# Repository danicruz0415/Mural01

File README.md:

# Mural01
Design files, 3D models, cuts and circuits used for my first mural

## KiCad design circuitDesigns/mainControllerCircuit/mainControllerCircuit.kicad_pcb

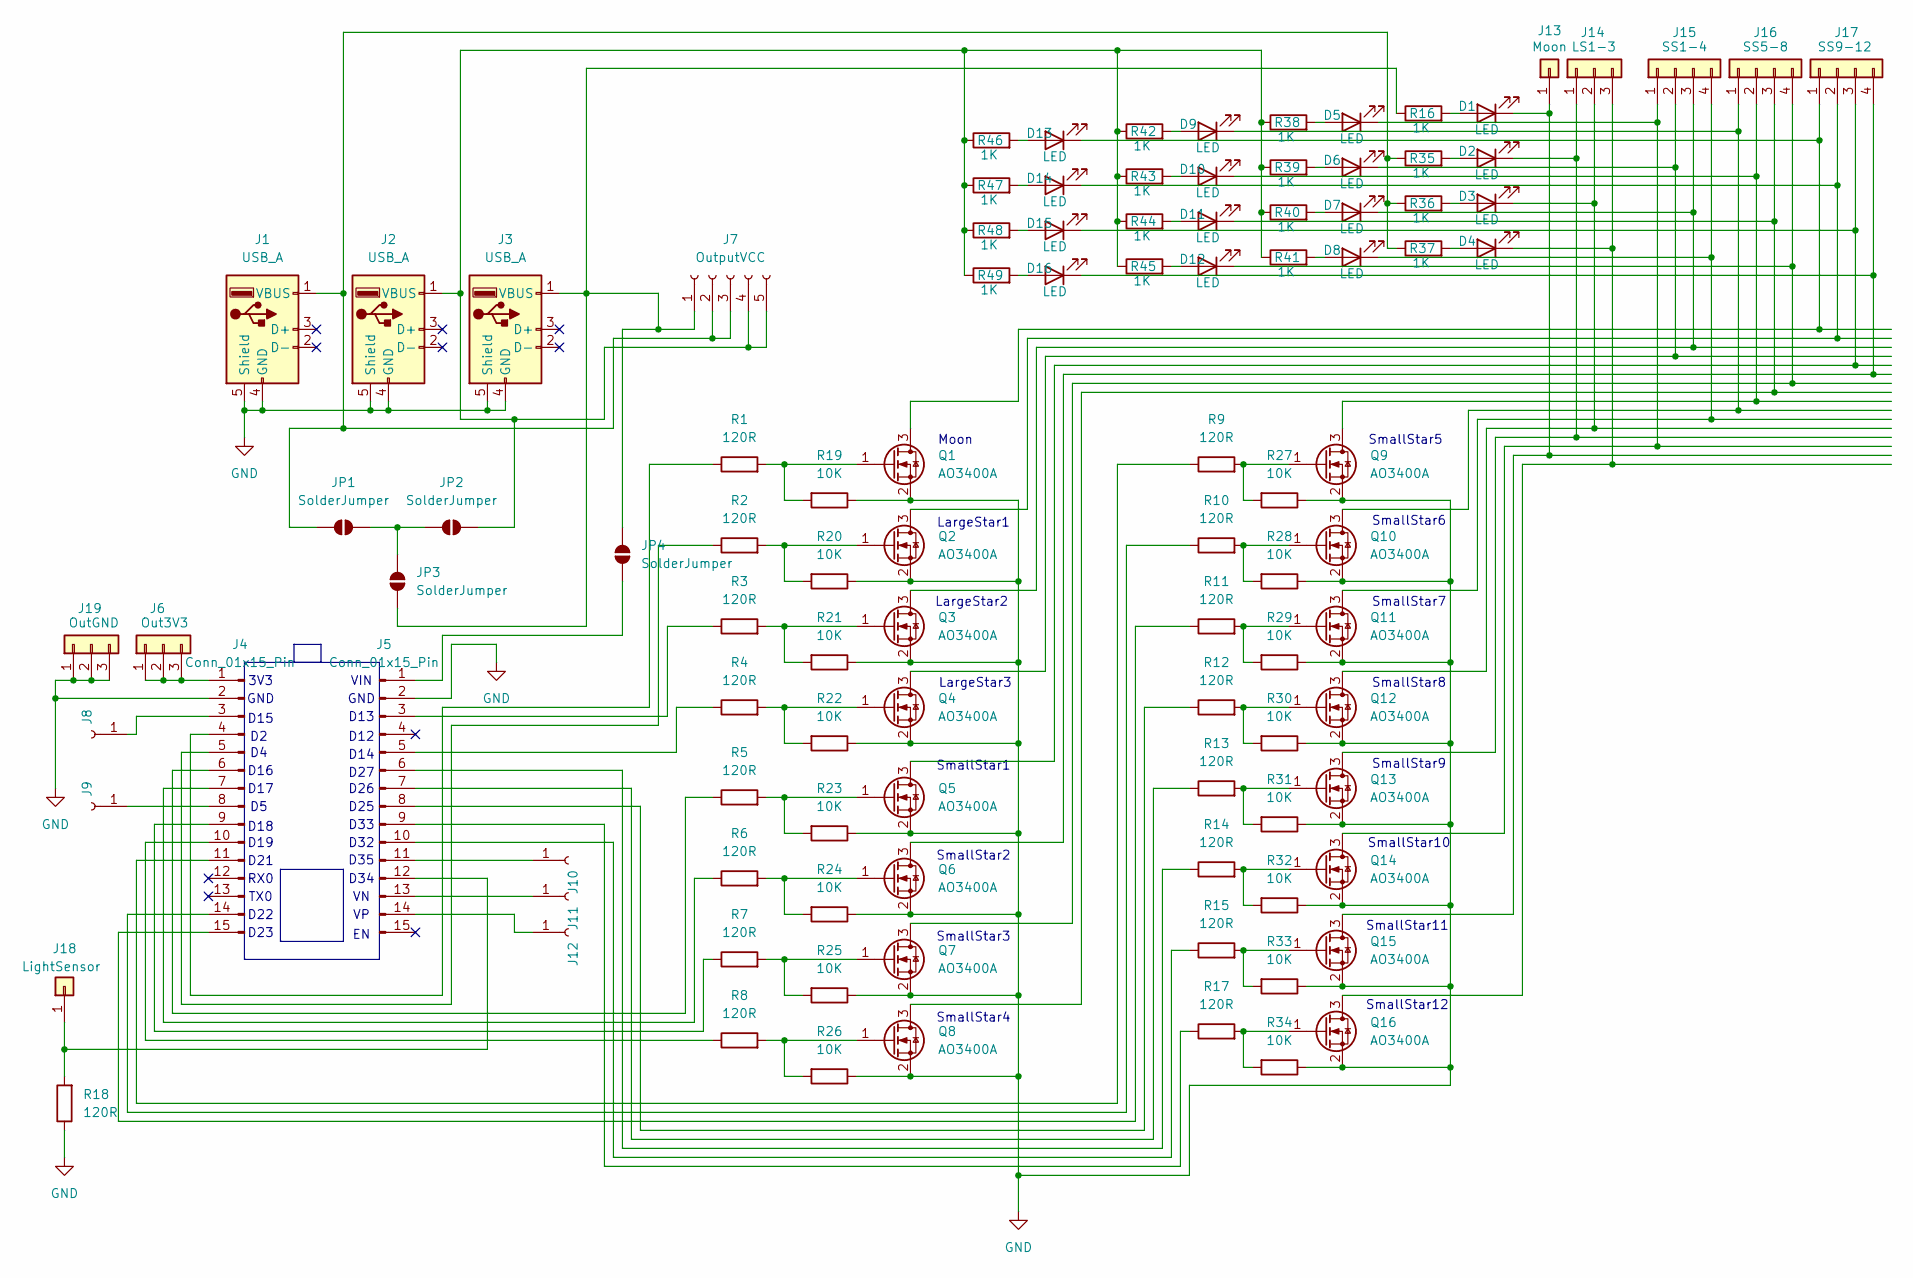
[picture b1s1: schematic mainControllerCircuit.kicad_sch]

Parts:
D1, D2, D3, D4, D5, D6, D7, D8, D9, D10, D11, D12, D13, D14, D15, D16: LED; LED_D3.0mm
J1, J2, J3: USB_A; USB_A_Molex_67643_Horizontal
J4, J5: Conn_01x15_Pin; PinSocket_1x15_P2.54mm_Vertical
J6: Out3V3; PinSocket_1x03_P2.54mm_Vertical
J7: OutputVCC; PinSocket_1x05_P2.54mm_Vertical
J8, J9, J10, J11, J12: PinSocket_1x01_P2.54mm_Vertical
J13: Moon; PinSocket_1x01_P2.54mm_Vertical
J14: LS1-3; PinSocket_1x03_P2.54mm_Vertical
J15: SS1-4; PinSocket_1x04_P2.54mm_Vertical
J16: SS5-8; PinSocket_1x04_P2.54mm_Vertical
J17: SS9-12; PinSocket_1x04_P2.54mm_Vertical
J18: LightSensor; PinSocket_1x01_P2.54mm_Vertical
J19: OutGND; PinSocket_1x03_P2.54mm_Vertical
JP1, JP2, JP3, JP4: SolderJumper; PinSocket_1x02_P2.54mm_Vertical
Q1, Q2, Q3, Q4, Q5, Q6, Q7, Q8, Q9, Q10, Q11, Q12, Q13, Q14, Q15, Q16: AO3400A; SOT-23
R1, R2, R3, R4, R5, R6, R7, R8, R9, R10, R11, R12, R13, R14, R15, R17, R18: 120R; R_Axial_DIN0207_L6.3mm_D2.5mm_P7.62mm_Horizontal
R16, R35, R36, R37, R38, R39, R40, R41, R42, R43, R44, R45, R46, R47, R48, R49: 1K; R_Axial_DIN0207_L6.3mm_D2.5mm_P7.62mm_Horizontal
R19, R20, R21, R22, R23, R24, R25, R26, R27, R28, R29, R30, R31, R32, R33, R34: 10K; R_Axial_DIN0207_L6.3mm_D2.5mm_P7.62mm_Horizontal

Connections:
GND: J1.4 (GND), J1.5 (Shield), J2.4 (GND), J2.5 (Shield), J3.4 (GND), J3.5 (Shield), J4.2, J5.2, J19.1, J19.2, J19.3, Q1.2 (S), Q2.2 (S), Q3.2 (S), Q4.2 (S), Q5.2 (S), Q6.2 (S), Q7.2 (S), Q8.2 (S), Q9.2 (S), Q10.2 (S), Q11.2 (S), Q12.2 (S), Q13.2 (S), Q14.2 (S), Q15.2 (S), Q16.2 (S), R18.1, R19.1, R20.1, R21.1, R22.1, R23.1, R24.1, R25.1, R26.1, R27.1, R28.1, R29.1, R30.1, R31.1, R32.1, R33.1, R34.1
unnamed: D1.2 (A), R16.2
unnamed: D1.1 (K), J13.1, Q15.3 (D)
unnamed: D2.2 (A), R35.2
unnamed: D2.1 (K), J14.1, Q13.3 (D)
unnamed: D3.2 (A), R36.2
unnamed: D3.1 (K), J14.2, Q12.3 (D)
unnamed: D4.2 (A), R37.2
unnamed: D4.1 (K), J14.3, Q16.3 (D)
unnamed: D5.2 (A), R38.2
unnamed: D5.1 (K), J15.1, Q14.3 (D)
unnamed: D6.2 (A), R39.2
unnamed: D6.1 (K), J15.2, Q4.3 (D)
unnamed: D7.2 (A), R40.2
unnamed: D7.1 (K), J15.3, Q3.3 (D)
unnamed: D8.2 (A), R41.2
unnamed: D8.1 (K), J15.4, Q11.3 (D)
unnamed: D9.2 (A), R42.2
unnamed: D9.1 (K), J16.1, Q10.3 (D)
unnamed: D10.2 (A), R43.2
unnamed: D10.1 (K), J16.2, Q9.3 (D)
unnamed: D11.2 (A), R44.2
unnamed: D11.1 (K), J16.3, Q8.3 (D)
unnamed: D12.2 (A), R45.2
unnamed: D12.1 (K), J16.4, Q7.3 (D)
unnamed: D13.2 (A), R46.2
unnamed: D13.1 (K), J17.1, Q1.3 (D)
unnamed: D14.2 (A), R47.2
unnamed: D14.1 (K), J17.2, Q2.3 (D)
unnamed: D15.2 (A), R48.2
unnamed: D15.1 (K), J17.3, Q5.3 (D)
unnamed: D16.2 (A), R49.2
unnamed: D16.1 (K), J17.4, Q6.3 (D)
unnamed: J1.1 (VBUS), J7.2, J7.3, JP1.2 (B), R35.1, R36.1, R37.1
unnamed: J2.1 (VBUS), J7.4, J7.5, JP2.2 (B), R38.1, R39.1, R40.1, R41.1, R42.1, R43.1, R44.1, R45.1, R46.1, R47.1, R48.1, R49.1
unnamed: J3.1 (VBUS), J7.1, JP3.1 (A), JP4.2 (B), R16.1
unnamed: J4.1, J6.1, J6.2, J6.3
unnamed: J4.3, J8.1
unnamed: J4.4, R1.1
unnamed: J4.5, R2.1
unnamed: J4.6, R5.1
unnamed: J4.7, R6.1
unnamed: J4.8, J9.1
unnamed: J4.9, R7.1
unnamed: J4.10, R8.1
unnamed: J4.11, R9.1
unnamed: J4.14, R10.1
unnamed: J4.15, R11.1
unnamed: J5.1, JP4.1 (A)
unnamed: J5.3, R3.1
unnamed: J5.5, R4.1
unnamed: J5.6, R14.1
unnamed: J5.7, R13.1
unnamed: J5.8, R12.1
unnamed: J5.9, R17.1
unnamed: J5.10, R15.1
unnamed: J5.11, J10.1
unnamed: J5.13, J11.1
unnamed: J5.14, J12.1
unnamed: J5.12, J18.1, R18.2
unnamed: JP1.1 (A), JP2.1 (A), JP3.2 (B)
unnamed: Q1.1 (G), R1.2, R19.2
unnamed: Q2.1 (G), R2.2, R20.2
unnamed: Q3.1 (G), R3.2, R21.2
unnamed: Q4.1 (G), R4.2, R22.2
unnamed: Q5.1 (G), R5.2, R23.2
unnamed: Q6.1 (G), R6.2, R24.2
unnamed: Q7.1 (G), R7.2, R25.2
unnamed: Q8.1 (G), R8.2, R26.2
unnamed: Q9.1 (G), R9.2, R27.2
unnamed: Q10.1 (G), R10.2, R28.2
unnamed: Q11.1 (G), R11.2, R29.2
unnamed: Q12.1 (G), R12.2, R30.2
unnamed: Q13.1 (G), R13.2, R31.2
unnamed: Q14.1 (G), R14.2, R32.2
unnamed: Q15.1 (G), R15.2, R33.2
unnamed: Q16.1 (G), R17.2, R34.2

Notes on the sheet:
D26
GND
SmallStar11
TX0
SmallStar4
3V3
D14
D33
D15
D35
D16
VIN
LargeStar3
D17
Moon
D22
LargeStar1
SmallStar10
D19
D27
D12
SmallStar6
D23
SmallStar5
SmallStar7
RX0
SmallStar3
LargeStar2
D25
D18
D21
SmallStar9
D32
SmallStar2
D34
SmallStar1
SmallStar12
SmallStar8
D13

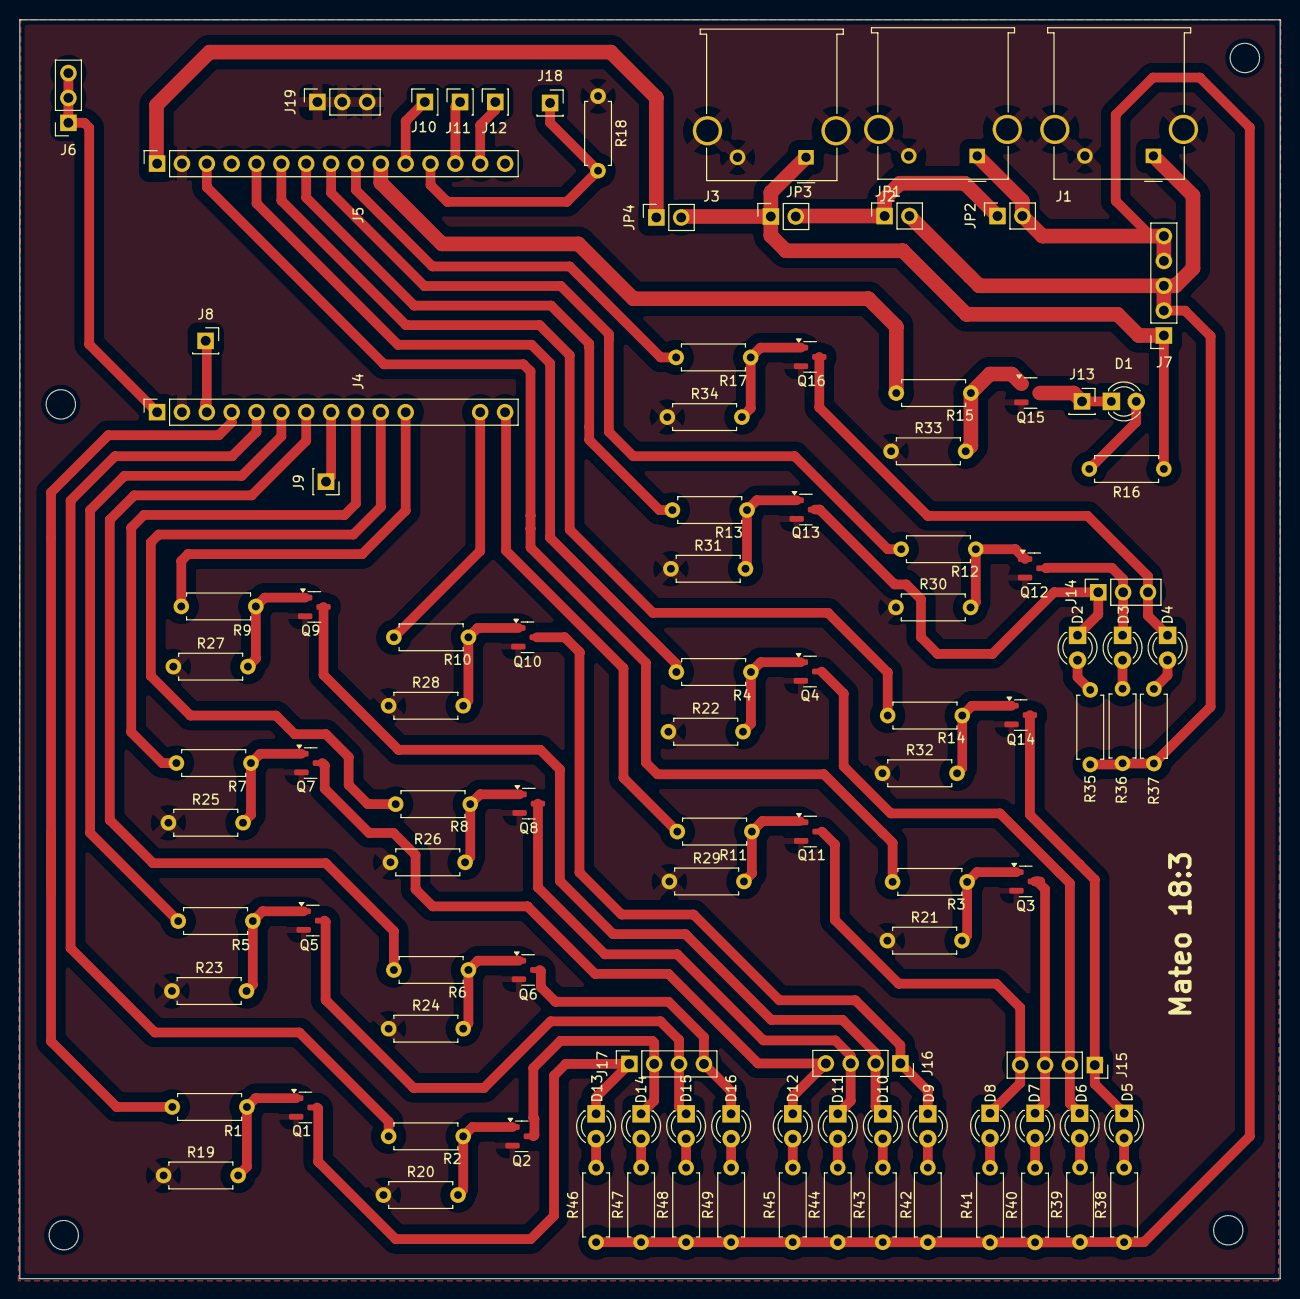
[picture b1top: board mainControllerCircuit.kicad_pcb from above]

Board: 2 copper layers, 128.8 x 128.6 mm, 104 parts (0 on the bottom side), 77 nets.

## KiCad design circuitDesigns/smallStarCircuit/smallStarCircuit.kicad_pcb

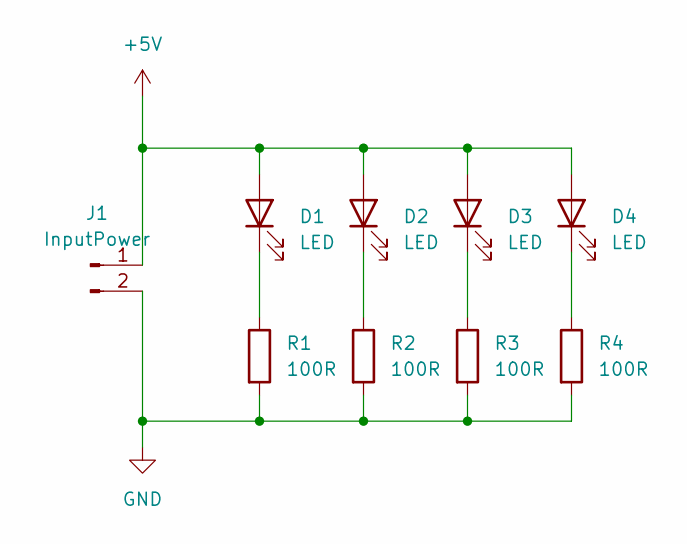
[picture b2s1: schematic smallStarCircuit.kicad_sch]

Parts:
D1, D2, D3, D4: LED; Custom5050LED
J1: InputPower; CustomIOConnector
R1, R2, R3, R4: 100R; R_1206_3216Metric_Pad1.30x1.75mm_HandSolder

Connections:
+5V: D1.2 (A), D2.2 (A), D3.2 (A), D4.2 (A), J1.1
GND: J1.2, R1.2, R2.2, R3.2, R4.2
unnamed: D1.1 (K), R1.1
unnamed: D2.1 (K), R2.1
unnamed: D3.1 (K), R3.1
unnamed: D4.1 (K), R4.1

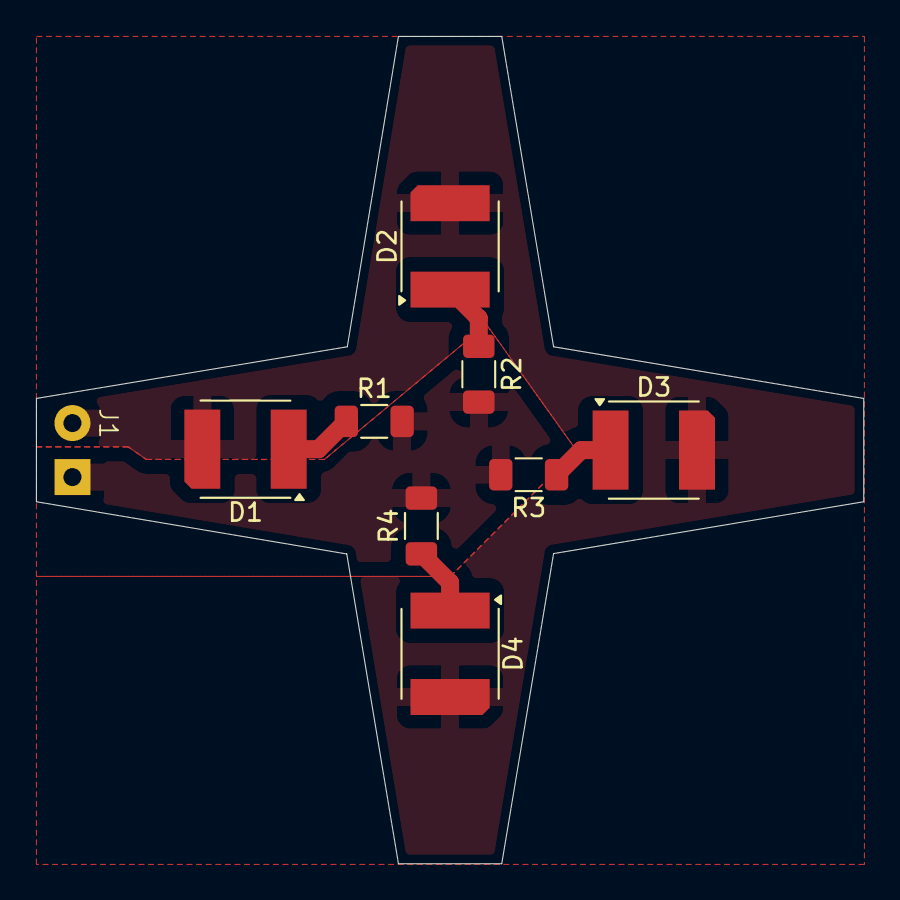
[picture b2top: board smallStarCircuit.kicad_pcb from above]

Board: 2 copper layers, 46.0 x 46.0 mm, 9 parts (0 on the bottom side), 6 nets.

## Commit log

2025-10-09 cleans up gitignore
2025-10-09 Adds illumination controller program
2025-10-09 Adds design files for cuts, circuits and 3D printable parts
2025-10-11 Leaves only final mural design
2025-10-11 Updates design files for main controller to better accomodate to manufacturer specs
2025-10-12 Increases clearances between the pads to not have a safer margin above the minimum limits of the manufacturer
2025-10-14 Improves circuit design adding better clearances and using thermal relieves on power planes
2025-10-14 Adds corner to custom's 5050LED footprint, to distiguish polarity and to give extra room for the power to pass right next to the LED on the edges
2025-10-15 Adds local gitignore to not track kicad backups
2025-10-15 Improves circuit design by adding thermal relieves and improving the position of ground and power planes
2025-10-19 Fixes error in controller circuit: mosfets were missing pull down resistor
2025-10-19 Adds LED indicators to the main controller board
2025-10-19 Adds mounting holes to the main controller's PCB
2025-10-19 Increases the thickness for the trace of the moon controller as its the one that will handle the most current. Fixes missing ground connection
2025-10-19 Removes reference rects
2025-10-19 Adds quote to the main controller board
2025-10-28 Updates design to match current wall dimentions. Relocates star positions. Adds star to complete 12 stars
2025-10-28 Updates pins for stars to match the last circuit design. Updates analog write res and framerate.
2025-10-28 Fixes shape that was out of bounds in image design
2025-10-28 Fixes document properties in image design so that it covers the whole image
2025-10-28 Adds design for external wiring
2025-10-30 Adds power lines to external wiring diagram
2025-11-04 Reallocates cut files. Add cuts for mirrors and wire paths for large star design and moon design
2025-11-04 Cleans up lock files
2025-11-04 Adds color squema to external wiring
2025-11-04 Adds monitor speed to platformio config
2025-11-07 Updates design to reflect the moons angle more closely to how it appears where the mural will be painted, and improves the colors
2025-11-10 Adds one more layer to the design. Adds gradients to convey depth
2025-11-10 Adds cut that represents the moon's silhouette
2025-11-16 Adds mural design rendered version
2025-11-16 Adds design preview to the readme
